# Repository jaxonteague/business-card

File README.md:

# Business Card - Floppy Bird

I wanted my business card to do more than sit in someone's wallet, so I built
one with a custom PCB, 128 RGB LEDs, and a playable game called **Floppy Bird**.
It brings together PCB design, embedded C, real-time game logic, all displayed on
a 16x8 custom led mattrix display.

## What it does

Floppy Bird is controlled with a single physical button. Pressing it makes the
bird flap while two-pixel-wide pipes move across the display. Passing a pipe
earns a point, and the game gradually speeds up across ten difficulty levels.

The player gets three lives. Once all three lives are gone, the final score
appears.

## What I built

- A custom KiCad schematic and PCB for an STM32C031 and 8x16 addressable RGB
  LED matrix.
- A framebuffer-based LED driver that converts RGB values into WS2812 data and
  sends each frame using SPI with DMA.
- Non-blocking game logic covering bird physics, random pipe gaps, collisions,
  lives, scoring, difficulty progression, and game-over handling.
- Interrupt-driven button input with the actual game update kept in the main
  loop, keeping the interrupt handler short.
- Low-power idle time using the Cortex-M0+ wait-for-interrupt instruction.
- Production files including Gerbers, a bill of materials, and component
  placement data.

## Hardware

At the centre of the card is an STM32C031, a small Cortex-M0+ microcontroller
that handles the game, button input, and LED data. The display is made from 128
individually addressable RGB LEDs arranged as 16 columns by 8 rows. A single
physical button provides the game input, keeping the interface simple and making
the card immediately playable.

The card is powered by two AAA batteries. A boost converter raises the battery
voltage to 5 V for the LED matrix, while an LDO steps that rail down to 3.3 V for
the microcontroller. Because the STM32 and LEDs operate at different logic
levels, a level converter shifts the 3.3 V SPI data signal up to 5 V before it
reaches the LEDs. The button input is debounced in hardware with an RC filter so
a single press produces a clean, reliable transition.

The LEDs share one serial data chain and are updated from an SPI peripheral using
DMA. This lets the microcontroller transfer a complete frame in the background
instead of spending all of its time manually generating the LED waveform.

Power consumption was an important part of the design because 128 RGB LEDs can
draw a lot of current at full output. The firmware keeps brightness deliberately
low, and the hardware includes local decoupling for the LED supply.

While the led matrix is cool, it is quite power hungry. Drawing 3/4W, the display
will run for 4-6 hours from 2x AAA batteries.

PCB is 2 layer double sided. The matrix is connected in alternate directions so
as to simpliy routing and avoid unnecessary trace lengths.

## A few interesting details

The LEDs are routed in a serpentine pattern on the PCB. The driver translates
normal `(x, y)` coordinates into the physical LED order, so the game code does
not need to know how the traces are laid out.

The bird uses fixed-point physics instead of floating point. This makes its
movement smoother than jumping directly between the eight rows while staying
lightweight for the Cortex-M0+ microcontroller. Fractional accumulators give
fine control over gravity and pipe speed without floating-point overhead.

The firmware is split into small modules: game logic and rendering are separate
from the LED driver, and adjustable gameplay values live in one configuration
header.

The leds are very bright, so to same battery and eyesight, they are set to very
low brightness.

## Tools and technologies

- Embedded C
- STM32C031 microcontroller
- STM32CubeMX and STM32CubeIDE
- GPIO interrupts, SPI, DMA, and low-power operation
- WS2812-compatible RGB LEDs
- Fixed-point arithmetic and real-time state machines
- KiCad schematic capture and PCB layout
- Design-for-manufacture files for JLCPCB

## Repository contents

The `pcb` folder contains the KiCad design and manufacturing files. The STM32
firmware is in `microcontroller/business card`.

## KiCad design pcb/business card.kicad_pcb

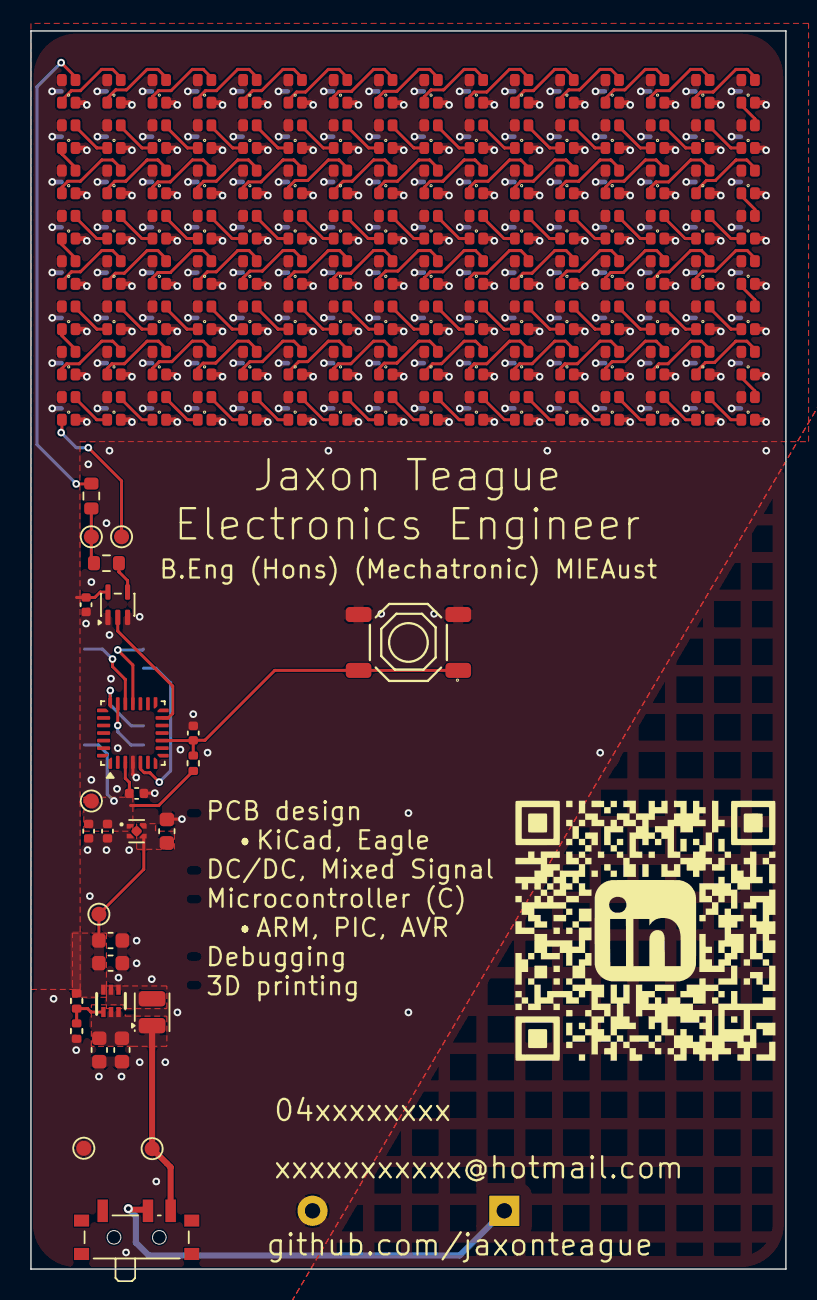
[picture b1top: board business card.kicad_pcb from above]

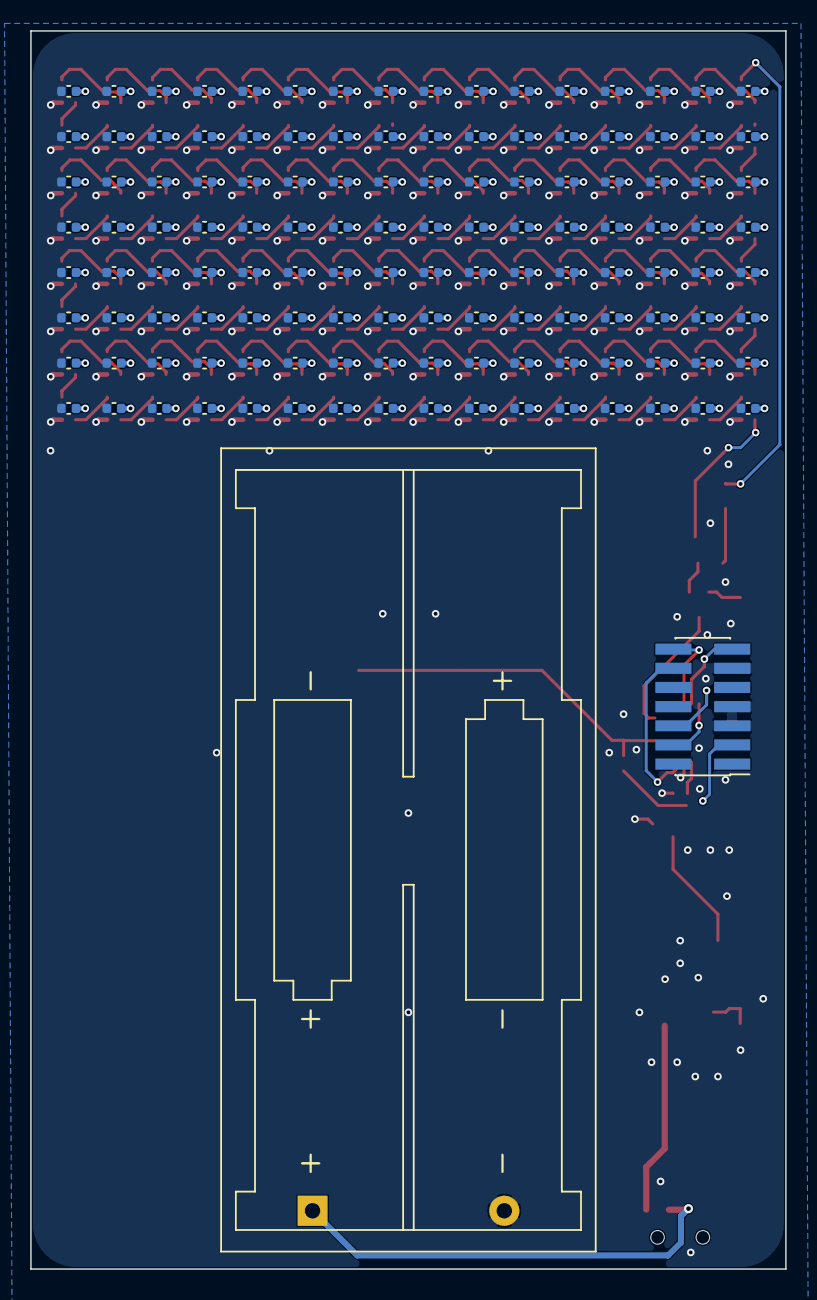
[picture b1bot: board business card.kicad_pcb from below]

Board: 2 copper layers, 50.0 x 82.0 mm, 286 parts (130 on the bottom side), 145 nets.

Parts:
BT1: Battery; BatteryHolder_Keystone_2468_2xAAA
C1, C2, C3, C4: 10uF; C_0603_1608Metric
C5: 2.2uF; C_0603_1608Metric
C6, C8, C9, C10, C11, C12, C13, C14, C15, C16, C17, C18, C19, C20, C21, C22, C23, C24, C25, C26, C27, C28, C29, C30, C31, C32, C33, C34, C35, C36, C37, C38, C39, C40, C41, C42, C43, C44, C45, C46, C47, C48, C49, C50, C51, C52, C53, C54, C55, C56, C57, C58, C59, C60, C61, C62, C63, C64, C65, C66, C67, C68, C69, C70, C71, C72, C73, C74, C75, C76, C77, C78, C79, C80, C81, C82, C83, C84, C85, C86, C87, C88, C89, C90, C91, C92, C93, C94, C95, C96, C97, C98, C99, C100, C101, C102, C103, C104, C105, C106, C107, C108, C109, C110, C111, C112, C113, C114, C115, C116, C117, C118, C119, C120, C121, C122, C123, C124, C125, C126, C127, C128, C129, C130, C131, C132, C133, C134, C135, C136, C137, C138: 100nF; C_0402_1005Metric
C7: 10uF; C_0402_1005Metric
D1, D2, D3, D4, D5, D6, D7, D8, D9, D10, D11, D12, D13, D14, D15, D16, D17, D18, D19, D20, D21, D22, D23, D24, D25, D26, D27, D28, D29, D30, D31, D32, D33, D34, D35, D36, D37, D38, D39, D40, D41, D42, D43, D44, D45, D46, D47, D48, D49, D50, D51, D52, D53, D54, D55, D56, D57, D58, D59, D60, D61, D62, D63, D64, D65, D66, D67, D68, D69, D70, D71, D72, D73, D74, D75, D76, D77, D78, D79, D80, D81, D82, D83, D84, D85, D86, D87, D88, D89, D90, D91, D92, D93, D94, D95, D96, D97, D98, D99, D100, D101, D102, D103, D104, D105, D106, D107, D108, D109, D110, D111, D112, D113, D114, D115, D116, D117, D118, D119, D120, D121, D122, D123, D124, D125, D126, D127, D128: WS2812B; LED-SMD_4P-L1.6-W1.5_XL-1615RGBC-WS2812B
J1: Conn_ST_STDC14; PinHeader_2x07_P1.27mm_Vertical_SMD
L1: 470nH; L_Coilcraft_0805HQ_2012Metric
R1: 100; R_0603_1608Metric
R3: 732k; R_0402_1005Metric
R4, R5: 100k; R_0402_1005Metric
R6: 0R; R_0603_1608Metric
S1: Tactile Button, 160gf; SW-SMD_4P-L5.1-W5.1-P3.70-LS6.5-TL-2
SW1: SW_SPDT; SW_SPDT_PCM12
TP1, TP2, TP3, TP4, TP5, TP6: TestPoint_Probe; TestPoint_Pad_D1.0mm
U1: STM32C031G6Ux; QFN-28_4x4mm_P0.5mm
U2: TPS61023DRLR; DRL0006A
U3: TLV71333PDBV; Texas_X2SON-4_1x1mm_P0.65mm
U4: 74AHCT1G125; SOT-353_SC-70-5

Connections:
+3V3: C6.1, C7.1, C8.1, J1.3 (VCC), R5.1, TP3.1 (1_1), U1.3 (VDD), U3.1 (OUT)
+5V: C3.1, C4.1, C5.1, C9.1, C11.1, C12.1, C13.1, C14.1, C15.1, C16.1, C17.1, C18.1, C19.1, C20.1, C21.1, C22.1, C23.1, C24.1, C25.1, C26.1, C27.1, C28.1, C29.1, C30.1, C31.1, C32.1, C33.1, C34.1, C35.1, C36.1, C37.1, C38.1, C39.1, C40.1, C41.1, C42.1, C43.1, C44.1, C45.1, C46.1, C47.1, C48.1, C49.1, C50.1, C51.1, C52.1, C53.1, C54.1, C55.1, C56.1, C57.1, C58.1, C59.1, C60.1, C61.1, C62.1, C63.1, C64.1, C65.1, C66.1, C67.1, C68.1, C69.1, C70.1, C71.1, C72.1, C73.1, C74.1, C75.1, C76.1, C77.1, C78.1, C79.1, C80.1, C81.1, C82.1, C83.1, C84.1, C85.1, C86.1, C87.1, C88.1, C89.1, C90.1, C91.1, C92.1, C93.1, C94.1, C95.1, C96.1, C97.1, C98.1, C99.1, C100.1, C101.1, C102.1, C103.1, C104.1, C105.1, C106.1, C107.1, C108.1, C109.1, C110.1, C111.1, C112.1, C113.1, C114.1, C115.1, C116.1, C117.1, C118.1, C119.1, C120.1, C121.1, C122.1, C123.1, C124.1, C125.1, C126.1, C127.1, C128.1, C129.1, C130.1, C131.1, C132.1, C133.1, C134.1, C135.1, C136.1, C137.1, C138.1, D1.3 (VDD), D2.3 (VDD), D3.3 (VDD), D4.3 (VDD), D5.3 (VDD), D6.3 (VDD), D7.3 (VDD), D8.3 (VDD), D9.3 (VDD), D10.3 (VDD), D11.3 (VDD), D12.3 (VDD), D13.3 (VDD), D14.3 (VDD), D15.3 (VDD), D16.3 (VDD), D17.3 (VDD), D18.3 (VDD), D19.3 (VDD), D20.3 (VDD), D21.3 (VDD), D22.3 (VDD), D23.3 (VDD), D24.3 (VDD), D25.3 (VDD), D26.3 (VDD), D27.3 (VDD), D28.3 (VDD), D29.3 (VDD), D30.3 (VDD), D31.3 (VDD), D32.3 (VDD), D33.3 (VDD), D34.3 (VDD), D35.3 (VDD), D36.3 (VDD), D37.3 (VDD), D38.3 (VDD), D39.3 (VDD), D40.3 (VDD), D41.3 (VDD), D42.3 (VDD), D43.3 (VDD), D44.3 (VDD), D45.3 (VDD), D46.3 (VDD), D47.3 (VDD), D48.3 (VDD), D49.3 (VDD), D50.3 (VDD), D51.3 (VDD), D52.3 (VDD), D53.3 (VDD), D54.3 (VDD), D55.3 (VDD), D56.3 (VDD), D57.3 (VDD), D58.3 (VDD), D59.3 (VDD), D60.3 (VDD), D61.3 (VDD), D62.3 (VDD), D63.3 (VDD), D64.3 (VDD), D65.3 (VDD), D66.3 (VDD), D67.3 (VDD), D68.3 (VDD), D69.3 (VDD), D70.3 (VDD), D71.3 (VDD), D72.3 (VDD), D73.3 (VDD), D74.3 (VDD), D75.3 (VDD), D76.3 (VDD), D77.3 (VDD), D78.3 (VDD), D79.3 (VDD), D80.3 (VDD), D81.3 (VDD), D82.3 (VDD), D83.3 (VDD), D84.3 (VDD), D85.3 (VDD), D86.3 (VDD), D87.3 (VDD), D88.3 (VDD), D89.3 (VDD), D90.3 (VDD), D91.3 (VDD), D92.3 (VDD), D93.3 (VDD), D94.3 (VDD), D95.3 (VDD), D96.3 (VDD), D97.3 (VDD), D98.3 (VDD), D99.3 (VDD), D100.3 (VDD), D101.3 (VDD), D102.3 (VDD), D103.3 (VDD), D104.3 (VDD), D105.3 (VDD), D106.3 (VDD), D107.3 (VDD), D108.3 (VDD), D109.3 (VDD), D110.3 (VDD), D111.3 (VDD), D112.3 (VDD), D113.3 (VDD), D114.3 (VDD), D115.3 (VDD), D116.3 (VDD), D117.3 (VDD), D118.3 (VDD), D119.3 (VDD), D120.3 (VDD), D121.3 (VDD), D122.3 (VDD), D123.3 (VDD), D124.3 (VDD), D125.3 (VDD), D126.3 (VDD), D127.3 (VDD), D128.3 (VDD), R3.1, TP2.1 (1_1), U2.6 (VOUT), U3.3 (EN), U3.4 (IN), U4.5 (VCC)
+BATT: C1.1, C2.1, L1.1, SW1.3 (C), TP1.1 (1_1), U2.2 (EN), U2.3 (VIN)
/Button: C10.1, R5.2, S1.1 (A), S1.2 (B), U1.10 (PA4)
/RX: J1.13 (VCP_RX), U1.19 (PA12)
/SW: L1.2, U2.5 (SW)
/SWCLK: J1.6 (JCLK/SWCLK), U1.21 (PA14)
/SWDIO: J1.4 (JTMS/SWDIO), U1.20 (PA13)
/TX: J1.14 (VCP_TX), U1.18 (PA11)
/led_display/Din: D1.2 (DIN), R1.2
/led_display/Dout: D113.4 (DOUT), TP5.1 (1_1)
/pwr: BT1.1 (+), SW1.2 (B)
/~RESET: J1.12 (~RST), U1.5 (PF2)
GND: BT1.2 (-), C1.2, C2.2, C3.2, C4.2, C5.2, C6.2, C7.2, C8.2, C9.2, C10.2, C11.2, C12.2, C13.2, C14.2, C15.2, C16.2, C17.2, C18.2, C19.2, C20.2, C21.2, C22.2, C23.2, C24.2, C25.2, C26.2, C27.2, C28.2, C29.2, C30.2, C31.2, C32.2, C33.2, C34.2, C35.2, C36.2, C37.2, C38.2, C39.2, C40.2, C41.2, C42.2, C43.2, C44.2, C45.2, C46.2, C47.2, C48.2, C49.2, C50.2, C51.2, C52.2, C53.2, C54.2, C55.2, C56.2, C57.2, C58.2, C59.2, C60.2, C61.2, C62.2, C63.2, C64.2, C65.2, C66.2, C67.2, C68.2, C69.2, C70.2, C71.2, C72.2, C73.2, C74.2, C75.2, C76.2, C77.2, C78.2, C79.2, C80.2, C81.2, C82.2, C83.2, C84.2, C85.2, C86.2, C87.2, C88.2, C89.2, C90.2, C91.2, C92.2, C93.2, C94.2, C95.2, C96.2, C97.2, C98.2, C99.2, C100.2, C101.2, C102.2, C103.2, C104.2, C105.2, C106.2, C107.2, C108.2, C109.2, C110.2, C111.2, C112.2, C113.2, C114.2, C115.2, C116.2, C117.2, C118.2, C119.2, C120.2, C121.2, C122.2, C123.2, C124.2, C125.2, C126.2, C127.2, C128.2, C129.2, C130.2, C131.2, C132.2, C133.2, C134.2, C135.2, C136.2, C137.2, C138.2, D1.1 (GND), D2.1 (GND), D3.1 (GND), D4.1 (GND), D5.1 (GND), D6.1 (GND), D7.1 (GND), D8.1 (GND), D9.1 (GND), D10.1 (GND), D11.1 (GND), D12.1 (GND), D13.1 (GND), D14.1 (GND), D15.1 (GND), D16.1 (GND), D17.1 (GND), D18.1 (GND), D19.1 (GND), D20.1 (GND), D21.1 (GND), D22.1 (GND), D23.1 (GND), D24.1 (GND), D25.1 (GND), D26.1 (GND), D27.1 (GND), D28.1 (GND), D29.1 (GND), D30.1 (GND), D31.1 (GND), D32.1 (GND), D33.1 (GND), D34.1 (GND), D35.1 (GND), D36.1 (GND), D37.1 (GND), D38.1 (GND), D39.1 (GND), D40.1 (GND), D41.1 (GND), D42.1 (GND), D43.1 (GND), D44.1 (GND), D45.1 (GND), D46.1 (GND), D47.1 (GND), D48.1 (GND), D49.1 (GND), D50.1 (GND), D51.1 (GND), D52.1 (GND), D53.1 (GND), D54.1 (GND), D55.1 (GND), D56.1 (GND), D57.1 (GND), D58.1 (GND), D59.1 (GND), D60.1 (GND), D61.1 (GND), D62.1 (GND), D63.1 (GND), D64.1 (GND), D65.1 (GND), D66.1 (GND), D67.1 (GND), D68.1 (GND), D69.1 (GND), D70.1 (GND), D71.1 (GND), D72.1 (GND), D73.1 (GND), D74.1 (GND), D75.1 (GND), D76.1 (GND), D77.1 (GND), D78.1 (GND), D79.1 (GND), D80.1 (GND), D81.1 (GND), D82.1 (GND), D83.1 (GND), D84.1 (GND), D85.1 (GND), D86.1 (GND), D87.1 (GND), D88.1 (GND), D89.1 (GND), D90.1 (GND), D91.1 (GND), D92.1 (GND), D93.1 (GND), D94.1 (GND), D95.1 (GND), D96.1 (GND), D97.1 (GND), D98.1 (GND), D99.1 (GND), D100.1 (GND), D101.1 (GND), D102.1 (GND), D103.1 (GND), D104.1 (GND), D105.1 (GND), D106.1 (GND), D107.1 (GND), D108.1 (GND), D109.1 (GND), D110.1 (GND), D111.1 (GND), D112.1 (GND), D113.1 (GND), D114.1 (GND), D115.1 (GND), D116.1 (GND), D117.1 (GND), D118.1 (GND), D119.1 (GND), D120.1 (GND), D121.1 (GND), D122.1 (GND), D123.1 (GND), D124.1 (GND), D125.1 (GND), D126.1 (GND), D127.1 (GND), D128.1 (GND), J1.5 (GND), J1.7 (GND), J1.11 (GNDDetect), R4.2, S1.3 (C), S1.4 (D), TP6.1 (1_1), U1.4 (VSS), U2.4 (GND), U3.2 (GND), U4.1, U4.3 (GND)
unnamed: D1.4 (DOUT), D2.2 (DIN)
unnamed: D2.4 (DOUT), D3.2 (DIN)
unnamed: D3.4 (DOUT), D4.2 (DIN)
unnamed: D4.4 (DOUT), D5.2 (DIN)
unnamed: D5.4 (DOUT), D6.2 (DIN)
unnamed: D6.4 (DOUT), D7.2 (DIN)
unnamed: D7.4 (DOUT), D8.2 (DIN)
unnamed: D8.4 (DOUT), D9.2 (DIN)
unnamed: D9.4 (DOUT), D10.2 (DIN)
unnamed: D10.4 (DOUT), D11.2 (DIN)
unnamed: D11.4 (DOUT), D12.2 (DIN)
unnamed: D12.4 (DOUT), D13.2 (DIN)
unnamed: D13.4 (DOUT), D14.2 (DIN)
unnamed: D14.4 (DOUT), D15.2 (DIN)
unnamed: D15.4 (DOUT), D16.2 (DIN)
unnamed: D16.4 (DOUT), D32.2 (DIN)
unnamed: D17.2 (DIN), D18.4 (DOUT)
unnamed: D17.4 (DOUT), D33.2 (DIN)
unnamed: D18.2 (DIN), D19.4 (DOUT)
unnamed: D19.2 (DIN), D20.4 (DOUT)
unnamed: D20.2 (DIN), D21.4 (DOUT)
unnamed: D21.2 (DIN), D22.4 (DOUT)
unnamed: D22.2 (DIN), D23.4 (DOUT)
unnamed: D23.2 (DIN), D24.4 (DOUT)
unnamed: D24.2 (DIN), D25.4 (DOUT)
unnamed: D25.2 (DIN), D26.4 (DOUT)
unnamed: D26.2 (DIN), D27.4 (DOUT)
unnamed: D27.2 (DIN), D28.4 (DOUT)
unnamed: D28.2 (DIN), D29.4 (DOUT)
unnamed: D29.2 (DIN), D30.4 (DOUT)
unnamed: D30.2 (DIN), D31.4 (DOUT)
unnamed: D31.2 (DIN), D32.4 (DOUT)
unnamed: D33.4 (DOUT), D34.2 (DIN)
unnamed: D34.4 (DOUT), D35.2 (DIN)
unnamed: D35.4 (DOUT), D36.2 (DIN)
unnamed: D36.4 (DOUT), D37.2 (DIN)
unnamed: D37.4 (DOUT), D38.2 (DIN)
unnamed: D38.4 (DOUT), D39.2 (DIN)
unnamed: D39.4 (DOUT), D40.2 (DIN)
unnamed: D40.4 (DOUT), D41.2 (DIN)
unnamed: D41.4 (DOUT), D42.2 (DIN)
unnamed: D42.4 (DOUT), D43.2 (DIN)
unnamed: D43.4 (DOUT), D44.2 (DIN)
unnamed: D44.4 (DOUT), D45.2 (DIN)
unnamed: D45.4 (DOUT), D46.2 (DIN)
unnamed: D46.4 (DOUT), D47.2 (DIN)
unnamed: D47.4 (DOUT), D48.2 (DIN)
unnamed: D48.4 (DOUT), D64.2 (DIN)
unnamed: D49.2 (DIN), D50.4 (DOUT)
unnamed: D49.4 (DOUT), D65.2 (DIN)
unnamed: D50.2 (DIN), D51.4 (DOUT)
unnamed: D51.2 (DIN), D52.4 (DOUT)
unnamed: D52.2 (DIN), D53.4 (DOUT)
unnamed: D53.2 (DIN), D54.4 (DOUT)
unnamed: D54.2 (DIN), D55.4 (DOUT)
unnamed: D55.2 (DIN), D56.4 (DOUT)
unnamed: D56.2 (DIN), D57.4 (DOUT)
unnamed: D57.2 (DIN), D58.4 (DOUT)
unnamed: D58.2 (DIN), D59.4 (DOUT)
unnamed: D59.2 (DIN), D60.4 (DOUT)
unnamed: D60.2 (DIN), D61.4 (DOUT)
unnamed: D61.2 (DIN), D62.4 (DOUT)
unnamed: D62.2 (DIN), D63.4 (DOUT)
unnamed: D63.2 (DIN), D64.4 (DOUT)
unnamed: D65.4 (DOUT), D66.2 (DIN)
unnamed: D66.4 (DOUT), D67.2 (DIN)
unnamed: D67.4 (DOUT), D68.2 (DIN)
unnamed: D68.4 (DOUT), D69.2 (DIN)
unnamed: D69.4 (DOUT), D70.2 (DIN)
unnamed: D70.4 (DOUT), D71.2 (DIN)
unnamed: D71.4 (DOUT), D72.2 (DIN)
unnamed: D72.4 (DOUT), D73.2 (DIN)
unnamed: D73.4 (DOUT), D74.2 (DIN)
unnamed: D74.4 (DOUT), D75.2 (DIN)
unnamed: D75.4 (DOUT), D76.2 (DIN)
unnamed: D76.4 (DOUT), D77.2 (DIN)
unnamed: D77.4 (DOUT), D78.2 (DIN)
unnamed: D78.4 (DOUT), D79.2 (DIN)
unnamed: D79.4 (DOUT), D80.2 (DIN)
unnamed: D80.4 (DOUT), D96.2 (DIN)
unnamed: D81.2 (DIN), D82.4 (DOUT)
unnamed: D81.4 (DOUT), D97.2 (DIN)
unnamed: D82.2 (DIN), D83.4 (DOUT)
unnamed: D83.2 (DIN), D84.4 (DOUT)
unnamed: D84.2 (DIN), D85.4 (DOUT)
unnamed: D85.2 (DIN), D86.4 (DOUT)
unnamed: D86.2 (DIN), D87.4 (DOUT)
unnamed: D87.2 (DIN), D88.4 (DOUT)
unnamed: D88.2 (DIN), D89.4 (DOUT)
unnamed: D89.2 (DIN), D90.4 (DOUT)
unnamed: D90.2 (DIN), D91.4 (DOUT)
unnamed: D91.2 (DIN), D92.4 (DOUT)
unnamed: D92.2 (DIN), D93.4 (DOUT)
unnamed: D93.2 (DIN), D94.4 (DOUT)
unnamed: D94.2 (DIN), D95.4 (DOUT)
unnamed: D95.2 (DIN), D96.4 (DOUT)
unnamed: D97.4 (DOUT), D98.2 (DIN)
unnamed: D98.4 (DOUT), D99.2 (DIN)
unnamed: D99.4 (DOUT), D100.2 (DIN)
unnamed: D100.4 (DOUT), D101.2 (DIN)
unnamed: D101.4 (DOUT), D102.2 (DIN)
unnamed: D102.4 (DOUT), D103.2 (DIN)
unnamed: D103.4 (DOUT), D104.2 (DIN)
unnamed: D104.4 (DOUT), D105.2 (DIN)
unnamed: D105.4 (DOUT), D106.2 (DIN)
unnamed: D106.4 (DOUT), D107.2 (DIN)
unnamed: D107.4 (DOUT), D108.2 (DIN)
unnamed: D108.4 (DOUT), D109.2 (DIN)
unnamed: D109.4 (DOUT), D110.2 (DIN)
unnamed: D110.4 (DOUT), D111.2 (DIN)
unnamed: D111.4 (DOUT), D112.2 (DIN)
unnamed: D112.4 (DOUT), D128.2 (DIN)
unnamed: D113.2 (DIN), D114.4 (DOUT)
unnamed: D114.2 (DIN), D115.4 (DOUT)
unnamed: D115.2 (DIN), D116.4 (DOUT)
unnamed: D116.2 (DIN), D117.4 (DOUT)
unnamed: D117.2 (DIN), D118.4 (DOUT)
unnamed: D118.2 (DIN), D119.4 (DOUT)
unnamed: D119.2 (DIN), D120.4 (DOUT)
unnamed: D120.2 (DIN), D121.4 (DOUT)
unnamed: D121.2 (DIN), D122.4 (DOUT)
unnamed: D122.2 (DIN), D123.4 (DOUT)
unnamed: D123.2 (DIN), D124.4 (DOUT)
unnamed: D124.2 (DIN), D125.4 (DOUT)
unnamed: D125.2 (DIN), D126.4 (DOUT)
unnamed: D126.2 (DIN), D127.4 (DOUT)
unnamed: D127.2 (DIN), D128.4 (DOUT)
unnamed: R1.1, R6.2, TP4.1 (1_1)
unnamed: R6.1, U4.4
unnamed: U1.13 (PA7), U4.2
unnamed: R3.2, R4.1, U2.1 (FB)

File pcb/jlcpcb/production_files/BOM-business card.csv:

Comment,Designator,Footprint,LCSC,Quantity
0R,R6,R_0603_1608Metric,C21189,1
100,R1,R_0603_1608Metric,C22775,1
100k,"R4,R5",R_0402_1005Metric,C25741,2
100nF,"C10,C100,C101,C102,C103,C104,C105,C106,C107,C108,C109,C11,C110,C111,C112,C113,C114,C115,C116,C117,C118,C119,C12,C120,C121,C122,C123,C124,C125,C126,C127,C128,C129,C13,C130,C131,C132,C133,C134,C135,C136,C137,C138,C14,C15,C16,C17,C18,C19,C20,C21,C22,C23,C24,C25,C26,C27,C28,C29,C30,C31,C32,C33,C34,C35,C36,C37,C38,C39,C40,C41,C42,C43,C44,C45,C46,C47,C48,C49,C50,C51,C52,C53,C54,C55,C56,C57,C58,C59,C6,C60,C61,C62,C63,C64,C65,C66,C67,C68,C69,C70,C71,C72,C73,C74,C75,C76,C77,C78,C79,C8,C80,C81,C82,C83,C84,C85,C86,C87,C88,C89,C9,C90,C91,C92,C93,C94,C95,C96,C97,C98,C99",C_0402_1005Metric,C1525,132
10uF,C7,C_0402_1005Metric,C15525,1
10uF,"C1,C2,C3,C4",C_0603_1608Metric,C96446,4
2.2uF,C5,C_0603_1608Metric,C23630,1
470nH,L1,L_Coilcraft_0805HQ_2012Metric,C337914,1
732k,R3,R_0402_1005Metric,C409928,1
74AHCT1G125,U4,SOT-353_SC-70-5,C7039245,1
Battery,BT1,BatteryHolder_Keystone_2468_2xAAA,C254917,1
STM32C031G6Ux,U1,QFN-28_4x4mm_P0.5mm,C7324966,1
SW_SPDT,SW1,SW_SPDT_PCM12,C221841,1
TLV71333PDBV,U3,Texas_X2SON-4_1x1mm_P0.65mm,C90840,1
TPS61023DRLR,U2,DRL0006A,C919459,1
"Tactile Button, 160gf",S1,SW-SMD_4P-L5.1-W5.1-P3.70-LS6.5-TL-2,C318884,1
WS2812B,"D1,D10,D100,D101,D102,D103,D104,D105,D106,D107,D108,D109,D11,D110,D111,D112,D113,D114,D115,D116,D117,D118,D119,D12,D120,D121,D122,D123,D124,D125,D126,D127,D128,D13,D14,D15,D16,D17,D18,D19,D2,D20,D21,D22,D23,D24,D25,D26,D27,D28,D29,D3,D30,D31,D32,D33,D34,D35,D36,D37,D38,D39,D4,D40,D41,D42,D43,D44,D45,D46,D47,D48,D49,D5,D50,D51,D52,D53,D54,D55,D56,D57,D58,D59,D6,D60,D61,D62,D63,D64,D65,D66,D67,D68,D69,D7,D70,D71,D72,D73,D74,D75,D76,D77,D78,D79,D8,D80,D81,D82,D83,D84,D85,D86,D87,D88,D89,D9,D90,D91,D92,D93,D94,D95,D96,D97,D98,D99",LED-SMD_4P-L1.6-W1.5_XL-1615RGBC-WS2812B,C5349954,128
TestPoint_Probe,TP5,TestPoint_Pad_D1.0mm,,1
TestPoint_Probe,TP2,TestPoint_Pad_D1.0mm,,1
TestPoint_Probe,TP1,TestPoint_Pad_D1.0mm,,1
TestPoint_Probe,TP3,TestPoint_Pad_D1.0mm,,1
TestPoint_Probe,TP4,TestPoint_Pad_D1.0mm,,1
TestPoint_Probe,TP6,TestPoint_Pad_D1.0mm,,1
Conn_ST_STDC14,J1,PinHeader_2x07_P1.27mm_Vertical_SMD,,1

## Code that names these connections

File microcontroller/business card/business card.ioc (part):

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Mcu.Name=STM32C031G(4-6)Ux
Mcu.Package=UFQFPN28
Mcu.UserName=STM32C031G6Ux
PA1.Mode=TX_Only_Simplex_Unidirect_Master
PA1.Signal=SPI1_SCK
PA10\ [PA12].Mode=Asynchronous
PA10\ [PA12].Signal=USART1_RX
PA13.Mode=Serial_Wire
PA13.Signal=DEBUG_SWDIO
PA14-BOOT0.Mode=Serial_Wire
PA14-BOOT0.Signal=DEBUG_SWCLK
PA4.GPIOParameters=GPIO_Label,GPIO_ModeDefaultEXTI
PA4.GPIO_Label=Button
PA4.GPIO_ModeDefaultEXTI=GPIO_MODE_IT_FALLING
PA4.Signal=GPXTI4
PA7.GPIOParameters=GPIO_Speed,PinState,GPIO_PuPd,GPIO_Label,GPIO_Mode
PA7.GPIO_Label=Led_Data
PA7.GPIO_Mode=GPIO_MODE_AF_PP
PA7.GPIO_PuPd=GPIO_NOPULL
PA7.GPIO_Speed=GPIO_SPEED_FREQ_VERY_HIGH
PA7.Mode=TX_Only_Simplex_Unidirect_Master
PA7.PinState=GPIO_PIN_RESET
PA7.Signal=SPI1_MOSI
PA9\ [PA11].Mode=Asynchronous
PA9\ [PA11].Signal=USART1_TX
RCC.HSE_VALUE=8000000
RCC.SYSCLKFreq_VALUE=48000000
board=custom
